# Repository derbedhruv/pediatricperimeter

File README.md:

# pediatricperimeter
This contains all files for Pediatric Perimeter, imported from Karthik's repo. It will be looked at and modified into something purely in C++ by Sujeath

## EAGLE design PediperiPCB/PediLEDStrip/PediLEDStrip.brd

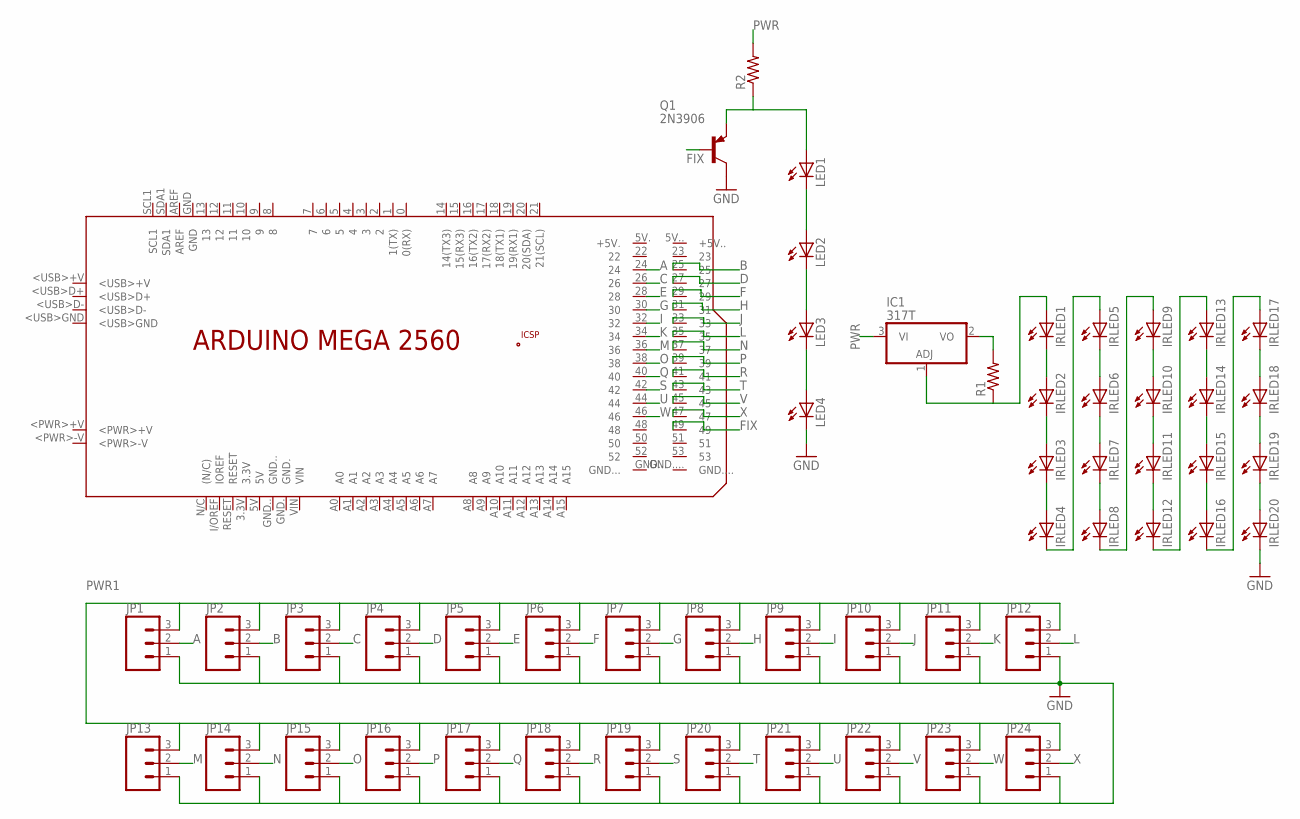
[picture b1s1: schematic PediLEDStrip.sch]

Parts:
IC1: 317T; TO220H
IRLED1, IRLED2, IRLED3, IRLED4, IRLED5, IRLED6, IRLED7, IRLED8, IRLED9, IRLED10, IRLED11, IRLED12, IRLED13, IRLED14, IRLED15, IRLED16, IRLED17, IRLED18, IRLED19, IRLED20: LED5MM
JP1, JP2, JP3, JP4, JP5, JP6, JP7, JP8, JP9, JP10, JP11, JP12, JP13, JP14, JP15, JP16, JP17, JP18, JP19, JP20, JP21, JP22, JP23, JP24: M03PTH; 1X03
LED1, LED2, LED3, LED4: LED5MM
PCB1: ARDUINO_MEGA2560
Q1: 2N3906; TO92
R1, R2: R-US_0207/10; 0207/10

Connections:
A: JP1.2, PCB1.24
B: JP2.2, PCB1.25
C: JP3.2, PCB1.26
D: JP4.2, PCB1.27
E: JP5.2, PCB1.28
F: JP6.2, PCB1.29
FIX: PCB1.49, Q1.2 (B)
G: JP7.2, PCB1.30
GND: IRLED20.K (C), JP1.1, JP2.1, JP3.1, JP4.1, JP5.1, JP6.1, JP7.1, JP8.1, JP9.1, JP10.1, JP11.1, JP12.1, JP13.1, JP14.1, JP15.1, JP16.1, JP17.1, JP18.1, JP19.1, JP20.1, JP21.1, JP22.1, JP23.1, JP24.1, LED4.K (C), Q1.1 (C)
H: JP8.2, PCB1.31
I: JP9.2, PCB1.32
J: JP10.2, PCB1.33
K: JP11.2, PCB1.34
L: JP12.2, PCB1.35
M: JP13.2, PCB1.36
N: JP14.2, PCB1.37
unnamed: LED1.K (C), LED2.A
unnamed: LED2.K (C), LED3.A
unnamed: LED3.K (C), LED4.A
unnamed: LED1.A, Q1.3 (E), R2.1
unnamed: IRLED1.K (C), IRLED2.A
unnamed: IRLED2.K (C), IRLED3.A
unnamed: IRLED3.K (C), IRLED4.A
unnamed: IRLED4.K (C), IRLED5.A
unnamed: IRLED5.K (C), IRLED6.A
unnamed: IRLED6.K (C), IRLED7.A
unnamed: IRLED7.K (C), IRLED8.A
unnamed: IRLED8.K (C), IRLED9.A
unnamed: IRLED9.K (C), IRLED10.A
unnamed: IRLED10.K (C), IRLED11.A
unnamed: IRLED11.K (C), IRLED12.A
unnamed: IRLED12.K (C), IRLED13.A
unnamed: IRLED13.K (C), IRLED14.A
unnamed: IRLED15.K (C), IRLED16.A
unnamed: IRLED14.K (C), IRLED15.A
unnamed: IRLED16.K (C), IRLED17.A
unnamed: IRLED17.K (C), IRLED18.A
unnamed: IRLED18.K (C), IRLED19.A
unnamed: IRLED19.K (C), IRLED20.A
unnamed: IC1.2 (VO), R1.2
unnamed: IC1.1 (ADJ), IRLED1.A, R1.1
O: JP15.2, PCB1.38
P: JP16.2, PCB1.39
PWR: IC1.3 (VI), R2.2
PWR1: JP1.3, JP2.3, JP3.3, JP4.3, JP5.3, JP6.3, JP7.3, JP8.3, JP9.3, JP10.3, JP11.3, JP12.3, JP13.3, JP14.3, JP15.3, JP16.3, JP17.3, JP18.3, JP19.3, JP20.3, JP21.3, JP22.3, JP23.3, JP24.3
Q: JP17.2, PCB1.40
R: JP18.2, PCB1.41
S: JP19.2, PCB1.42
T: JP20.2, PCB1.43
U: JP21.2, PCB1.44
V: JP22.2, PCB1.45
W: JP23.2, PCB1.46
X: JP24.2, PCB1.47

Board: 2 copper layers, 53 parts (1 on the bottom side), 53 nets, no tracks yet.

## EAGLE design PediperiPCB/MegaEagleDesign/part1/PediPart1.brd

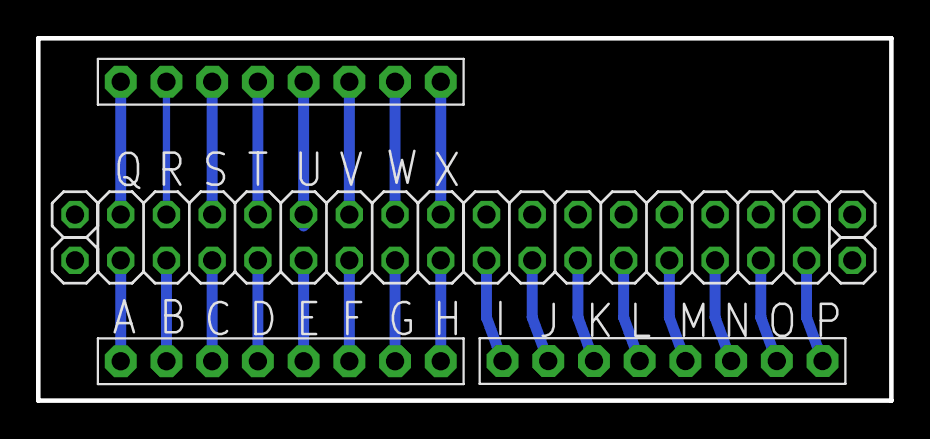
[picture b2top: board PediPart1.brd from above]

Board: 2 copper layers, 47.4 x 20.1 mm, 9 parts (0 on the bottom side), 23 nets.

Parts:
E$1, E$2, E$3: 1X08-BIG
JP1, JP2: 2X08
JP3, JP4, JP5, JP6: 1X01

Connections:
PC2: E$3.7, JP1.3
PC4: E$3.6, JP1.5
S$1: E$3.2, JP1.13
S$4: E$3.1, JP1.15
S$6: E$3.3, JP1.11
S$7: E$3.4, JP1.9
S$9: E$3.8, JP1.1
S$10: E$1.1, JP1.16
S$11: E$1.2, JP1.14
S$12: E$1.3, JP1.12
S$13: E$1.4, JP1.10
S$14: E$1.5, JP1.8
S$15: E$1.6, JP1.6
S$16: E$1.7, JP1.4
S$17: E$1.8, JP1.2
S$18: E$2.1, JP2.16
S$19: E$2.2, JP2.14
S$20: E$2.3, JP2.12
S$21: E$2.4, JP2.10
S$22: E$2.5, JP2.8
S$23: E$2.6, JP2.6
S$24: E$2.7, JP2.4
S$25: E$2.8, JP2.2

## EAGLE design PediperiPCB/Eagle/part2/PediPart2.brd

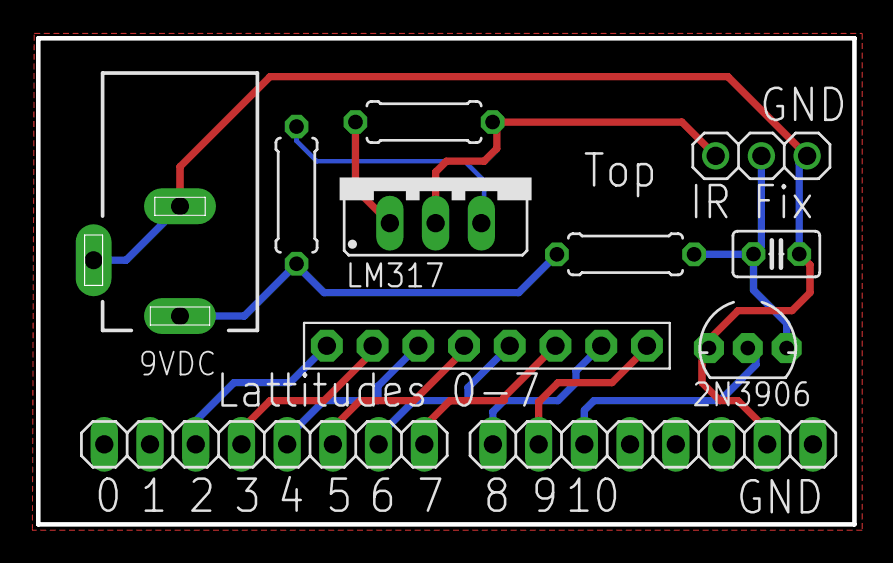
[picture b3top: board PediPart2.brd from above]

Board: 2 copper layers, 45.3 x 27.0 mm, 11 parts (0 on the bottom side), 15 nets.

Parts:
2N3906: TO92-INLINE
9VDC: DCJ0202
E$1: 1X08-BIG
E$2: 1X03
E$3: 12; 0207/7
E$4: 1K2; 0207/7
E$5: 470E; 0207/7
E$6: 10pF; C025-025X050
LM317: 78XXS
PWMH: 1X08
PWML: 1X08

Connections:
GND: 2N3906.1, 9VDC.2, 9VDC.3, E$2.3, E$6.2, PWMH.7
S$1: 9VDC.1, E$4.1, E$5.1
S$2: E$5.2, LM317.OUT
S$3: E$3.1, LM317.IN
S$4: E$2.1, E$3.2, LM317.GND
S$5: 2N3906.3, E$2.2, E$4.2, E$6.1
S$6: 2N3906.2, PWMH.3
S$7: E$1.1, PWML.3
S$8: E$1.2, PWML.4
S$9: E$1.3, PWML.5
S$10: E$1.4, PWML.6
S$11: E$1.5, PWML.7
S$12: E$1.6, PWML.8
S$13: E$1.7, PWMH.1
S$14: E$1.8, PWMH.2

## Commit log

2015-07-23 First Commit for the bucket
2015-07-23 Also added the Arduino Code and will update the same
2015-07-23 Added the CAD and the PCB Files
2015-07-23 Removed the CAD File
2015-07-23 Added the CAD File
2015-07-28 Added the Document for description
2015-07-28 Played the first Processing Sketch
2015-09-15 Adding the PCB and cabd files
2015-09-15 Added all
2015-09-15 Added the processing
2015-09-15 reentry
2015-09-15 Added the PCB files
2015-09-15 Added all the files
2015-09-22 Changes for the PCB are done the only change in the arduino code is the chenge of the fixation pin to pin number 10 from 11
2015-09-23 Updated the Resistor values for correction of intensity of LEDS
2015-09-30 Added the flex file for the flexible led case
2015-09-30 Removed the text edits and synced the schematic and board files
2015-10-03 done with the chenges in the file format of processing code
2015-10-28 Added the Random lights function on to the perimeter and also added the millisecond timestamp onto the text output
2015-11-20 Added the LED strip code for pediperi
2015-12-04 changed the video quality and hte video fps and also cleaned up the code lots
2015-12-08 Added the LED Strip
2015-12-08 Re arrange
2015-12-08 Donw with edits
2015-12-22 Camera feed + SDL output @ 25 fps
2015-12-22 Added CMakeLists.txt
2015-12-26 Changed main to test frame rate
2015-12-26 Added test.c Streams and views at VGA@51fps using V4L2. Compile command included Added test.c Streams and views at VGA@51fps using V4L2. Compile command included

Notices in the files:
parts and their libraries:
SparkFun-Connectors: Licensing: Creative Commons ShareAlike 4.0 International - https://creativecommons.org/licenses/by-sa/4.0
